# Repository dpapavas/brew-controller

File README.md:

<!-- -*- coding: utf-8 -*- -->

# Brew controller

This is a controller module designed as an add-on to the Gaggia Classic espresso
machine, although from a functional perspective it can be used with any "dumb"
espresso machine, i.e. any machine with a simple thermostat for boiler
temperature control and a simple on/off switch for pump control.  It can control
the brew process in both an automatic mode, following a programmed brew profile
based on flow, pressure and/or yield weight, or in manual mode, allowing direct,
real-time control of flow, pressure, or pump power.

## Design

The controller consists of the following parts:

* A pressure sensor, attached to the exit of the boiler, just before the group
  head.

* A flow sensor, attached to the pump inlet.

* A load cell, mounted below the drip tray, weighing the yielded coffee.

* A controller board, consisting of a pair of TRIAC switches, controlling power
  to the boiler and pump and a microcontroller, interfacing the sensors and
  controlling these switches.

* An enclosure and other assorted accessories, used to mount all the above to
  the espresso machine.

The design is freely available, but anyone considering their own build is urged
to read the discussion below, as there are some issues that will need to be
addressed.

## Operation

So, is this useful?  Well, yes, it is. All features, while arguably not
necessary, do offer additional useful control over the brewing process.
Temperature control improves temperature stability and control, allowing the
brewing to be adapted to the coffee at hand and, more importantly, improving the
consistency of the result across multiple shots.  Pump power control, makes
preinfusion possible and, in combination with pressure and flow measurement, it
also makes control of these parameters possible.  Pressure control is useful to
avoid channeling, while flow control can be useful, both to control preinfusion
where pressure has not yet developed and to give some control over brew time.
Weighing the yield allows automatic control of the brew ratio, as well as more
sensible variation of other parameters during the brew process (for instance the
pressure can be tapered off during the final third of the shot in terms of the
yield mass, instead of time).

The following plot is from data recorded by the controller during a programmed
shot.

The machine is already warmed up, as can be seen by the stable temperature (1)
and the small (less than 5% of the total) power needed at the boiler to maintain
it (2).  At about 12s the brew switch is pressed and the shot starts with a
preinfusion phase (3).  The pump is engaged at low power to push water through
the grounds at 3 ml/s.  As this happens, the temperature starts to drop, as cold
water enters the boiler, and power to the boiler is increased in order to
compensate.  Pressure gradually develops as the grounds expand and at 4 bars the
preinfusion phase is terminated (4).  Power to the pump is cut off, flow
vanishes and yield mass starts to rise as coffee starts to drip into the cup.

A blooming phase follows for the next 30s (5), where nothing much happens, apart
from temperature stabilization, a gradual drop-off in pressure and slight
increase in yield, as coffee leaks into the cup.  At 54s, the pump is engaged
once more, at higher power, and pressure is gradually ramped up to 9 bars (6).
Note the high initial flow, as the brew chamber is refilled, followed by a sharp
fall-off as the puck is compressed and pressure develops leading to oscillations
as the PID struggles somewhat to adapt to the complex dynamics.  This
necessitates both a gradual ramp-up in pressure (here from 0 to 9 bars in 5s) as
well as an additional wait time of 5s at 9 bars, while the flow settles.  After
that (7) the brew proceeds at constant flow rate, keeping the flow steady at the
1.7 ml/s it settled at.

In this particular shot, this strategy fails partially.  Maintaining the flow at
the instantaneous value measured at the end of the settling wait interval, leads
to a higher than desired flow and a pressure increase to a bit above 10 bars.
This can be corrected manually, if desired, either by reducing the flow to reduce
the developed pressure, or by reducing the pressure immediately.  No such action
has been taken here and the shot proceeds at a constant 10 bars and about 1.7
ml/s.  Note the disparity in volume and mass, the former of which is calculated
from the flow sensor, while the latter is measured via the load cell.  Some of
the difference is due to the water retained by the grounds, although most of
that has been accounted for, when the volume was reset at the end of the
preinfusion phase (4).  The rest of the difference is owed to inaccuracies in
the flow sensor, which accumulate as its signal is integrated to get the volume.

Finally the brew process is stopped at about 89s, with a total yield of 50g (8)
and pressure and flow drop to zero.  The sudden uptick in mass, is due to the
water remaining in the chamber being evacuated to the drip tray, via the
three-way solenoid valve.

A video recording of the controller brewing this exact shot, can be found
[here](https://youtu.be/QHlgAWKq7i8).

## Build

Although the design works quite well and is, at the time of this writing,
seemingly bug-free and refined enough for efficient and hassle-free daily use,
it does unfortunately suffer from a few design flaws that make it unsuitable for
anyone who might be considering building it.

For one, it was designed by someone that is not an electrical engineer.
Although as much care as possible was taken to ensure a good design, including
simulations and proper calculations where appropriate, the result does have a
few shortcomings which will probably need to be addressed:

* It is based on a Teensy 3.1/3.2 microcontroller, which is sadly no longer in
  production.  Any builds will therefore need to be ported to a more modern
  controller.  This problem is further compounded by the fact that the source
  code is "bare-metal", i.e. no hardware abstraction libraries are used, so that
  porting to a different controller is a non-trivial task.  Note though, that
  teasing out the application specific-code, i.e. the code implementing PID
  control, sensor signal reading and conditioning and rewriting the
  machine-specific parts, such as SPI, I2C, GPIO, timing and interrupt handling
  using a high-level library for the target controller, should not be a
  particularly hard task, given some experience.

* The coffee machine's brew switch, i.e. the one turning on the pump and
  starting the brewing process, is read through a GPIO input that is grounded
  via the switch.  The current design depends on the internal pull-up for this,
  which is too weak and hence prone to EMI.  This should probably be addressed in
  a potential board redesign, by including a stronger external pull-up resistor.

* In the current design, brewing is still controlled by the machine's brew
  switch, which is responsible for turning power to the pump on and off.  While
  this power can then be further controlled via the TRIAC, the three-way
  solenoid valve that is controlled by the same switch cannot.  Relegating this
  task to a relay, controlled by an additional GPIO output could therfore be
  useful, as it would allow automatically stopping the brew process, for
  instance when the desired yield has been achieved.  While this can be done
  now, one still needs to turn the switch off, to turn off the solenoid.  Doing
  this after the pump has been cut off, results in low pressure in the brew
  chamber and hence incomplete evacuation of the remaining brew water,
  nullifying the solenoid valve.

Due to the above, it is not expected that this design will be built by others.
The following discussion will therefore be limited to a general outline of the
build process.  Anyone intending to attempt a build is welcome to open an issue
for further clarifications.

### Parts

The parts needed to populate the board are the following:

|Designator|Description|
|----------|-----------|
|R3,R4|22KΩ, 1W through-hole resistor|
|R5|10KΩ, 1/4W through-hole resistor|
|U5|LD1117, 3.3V, TO-220-3 voltage regulator|
|C4,C2,C5|100nF through-hole ceramic resistor|
|D1|DB104, 400V, 1A bridge rectifier|
|R7,R6|360Ω, 1W through-hole resistor|
|Q1,Q2|2N7000, 0.2A, TO-92 N-Channel MOSFET|
|R8|680Ω, 1W through-hole resistor|
|U3,U2|MOC3021M, 400V optocoupler|
|Q3,Q4|BTA16-800CW 800V, TO-220-3 TRIAC|
|U4|Adafruit MAX31865 Module, or compatible|
|J4|JST XH 2-pin vertical connector|
|R2,R1|82Ω, 1/4W through-hole resistor|
|J2|Pin header, 2.54mm|
|J3|Pin header, 2.54mm|
|J5|Pin header, 2.54mm|
|U1|EL817 or PC817 optocoupler|
|C3|10u radial through-hole capacitor (low profile)|
|U6|Teensy 3.1 or 3.2|
|C1|100n, X2 through-hole capacitor|
|J1|5.08mm terminal block|

The following additional parts are also necessary:

* Heat sinks for the TRIACs.  Extruded aluminum heat sinks of size 46x20x10mm
  fit the enclosure and provide adequate cooling when properly mounted with heat
  sink compound.

* XP POWER ECL10US05-T 5V, 10W AC/DC power supply.

* Waveshare 1.5" RGB OLED Module, based on the SSD1351 controller.

* Waveshare rotation sensor, or similar push-button incremental rotary encoder.

* A PT100 temperature probe, preferably 3-wire.

* XDB-401 pressure sensor, in SS316L steel, 0-12 bar range, G1/8" thread, I2C
  interface.

* Shades Of Coffee Brew pressure gauge adaptor kit, or similar, along with a
  G1/8" female-to-female adaptor, to connect the pressure sensor to the boiler
  output.

* 3.3V hall-effect flow sensor.  The SEN-HZ06D can be used and has a suitably
  low range of 0.05-1.1 L/min.

* Adafruit NAU7802 24-Bit ADC module, or compatible.

* 1Kg 75x12.6x12.6mm load cell.  Mount holes should be M4, 10mm apart to fit the
  base and top plate.

* Shades of coffee slim drip tray.
 
* M3xM5x6mm threaded inserts for the enclosure.

* At least 1mm² silicon wire in various colors for high voltage/current wiring.

* Lower gauge silicon wire for the connection to the the espresso machine's brew
  switch.  Ideally of low enough gauge to allow crimping and fitting a
  Dupont-style terminal.

Finally, some parts need to be 3D printed.  See the [Things](#things) section
below.

# Assembly

Drill a total of six holes on the side of the espresso machine.  The 3D printed
mounting gasket can serve as a stencil to mark the locations and sizes of the
holes.  The four smaller peripheral holes serve to mount the enclosure.  Its
mounting bosses, where the threaded inserts are installed, should be able to
pass through those holes, barely protruding from the other side with the gasket
installed.  The two larger central holes serve to pass wiring into the espresso
machine.  One should be used for high voltage wiring and one for low voltage
wiring, to keep them separated.  Note that it is not absolutely necessary to
fully disassemble the espresso machine in order to drill the holes, although
that is the safest option.  With care, the operation can be carried out with
only the boiler screws and a few of its wires removed and the boiler simply held
out of the way, partially out of the machine.

Install the threaded inserts, assemble the controller board, including the
Teensy and TRIAC heat sinks and mount all boards onto the enclosure.  If the
supplied wiring brackets are used, it is recommended to glue the nuts on their
recesses, as they're otherwise held very loosely and can be a major source of
pain during assembly and repairs.

## Internal wiring

With the boards in place, the following internal wiring connections should be made:

* **Display module**: Attach the supplied 7-pin ribbon to the upper half
    (i.e. the part closest to the Teensy, marked `3V3`, `GND`, ..., `RST`) of
    the `J3` connector, noting the insertion orientation.

* **Rotary encoder**: Attach the supplied 5-pin ribbon to the `J2` connector on
    the board, noting the insertion orientation.

* **Supply**: Attach a suitable JST terminated cable from the output of the PSU
    board to the `J5` connector.  Although the connector is keyed, make sure the
    connector on the side of the controller board hasn't been soldered with
    incorrect orientation.  Also attach a 2-wire cable, terminated on one side
    with a suitable 3-pin JST connector to the input of the PSU board.  The bare
    wires on the other side, should be screwed into the terminal block plugged
    into the `J1` connector, in the pins marked `L` and `N`.  The polarity is
    not important.

After these steps, the assembled enclosure should look like this:

## Hardware assembly

Attach all external wiring (see below) to the appropriate controller connectors
and pass the wires through the two chassis holes, keeping high and low voltage
wires separated.  Place the enclosure so that the threaded bosses pass through
the holes drilled in the chassis and fasten it using the supplied countersunk
washers.  The lower washers can be hard to install, but it can be accomplished
using a short magnetic screw driver, if the boiler screws are removed and the
boiler moved out of the way, to gain access through the group head hole in the
chassis.  If the pressure sensor is used, its mount bracket should be used in
place of the washer for the upper hole closest to the middle of the machine.

Once the controller is fastened, the lower boiler thermostat should be removed
and replaced with the PT100 sensor.  The pressure sensor should also be
connected to the pressure gauge kit and mounted in the bracket, secured with a
zip tie passed through the slot in the back of the bracket.  The flow sensor
should be installed in line with the pressure inlet hose.

Two M4x12mm countersunk screws should be installed together with the supplied
"locating pins" in the holes at the top of the load cell base.  These form
locating bosses, mating with the holes at the bottom of the machine's chassis to
keep the base in place.  The load cell can be installed in either side, but the
right hand side is more convenient, as it facilitates the connections between
the controller module and both the load cell and the I2C bus.

The partially assembled scale looks like this:

The installed scale, can be seen [here](./doc/scale_installed.png).

## External wiring

The instructions below will be brief, intended more as a general strategy for
making the connections to the machine, rather than detailed instructions.  The
photograph should hopefully give a clearify the setup further, but please study
the wiring diagram first and take every care must be taken to ensure the proper
connections are made in a safe manner.

The proposed connections are for the EU model with the ECO timer module.  The
ECO timer will need to be bypassed, so as to gain access to a pair of contacts
at the brew switch for the controller sense connection. A simple wire with two
spade connectors is needed, but kits with installation instructions are also
sold online.

Note that live and neutral are treated loosely here and no care needs to or has
been taken to ensure that they correspond to the live and neutral at the
plug. They will therefore be indicated by "neutral" and "live" below.

### High voltage

* **"Neutral" input**: The "neutral" connection that powers the controller can
    be taken from the brew switch.  This requires a wire with three connectors
    on one end: one male spade connector plugging into the machine's "neutral"
    wire, after removing it from the brew switch, one female spade connector to
    restore the connection to the brew switch and another female spade
    connector, going back to the pump.

    The pump already has a connection for "neutral", but it passes through the
    brew switch, which creates a problem.  As the pump is switched off by the
    switch, back-EMF is created at the pump solenoid, leading to large voltage
    spikes and noise.  This can create all sorts of problems.  For instance it
    can pull the programming pin of the controller low and reboot it into
    programming mode, but it can also create I2C transmission problems, etc.
    Having an unswitched "neutral" connection allows the pump to be switched off
    via the TRIAC, which always ensures switching happens at zero current, hence
    no back-EMF or noise spikes.

    The other, unterminated end should be screwed into the controller's terminal
    block, at the place marked `N`, along with one of the small wires going to
    the PSU input.

* **"Live" input**: The live input can be taken from the lead going to the
    removed thermostat.  The other end should be screwed into to the
    controller's terminal block, at the place marked `L`, along with one of the
    other of the two small wires going to the PSU input.

* **Temperature control**: The other lead removed from the thermostat should be
    connected to the controller's terminal block, at the place marked `HEAT`.
    In this way, the controller's TRIAC switch essenatially assumes the place of
    the OEM thermostat switch.

* **Pump control**: The other terminal of the pump should be screwed into the
    controller's terminal block, at the place marked `PUMP`.  Note that the
    thermal fuse mounted on the pump is now by-passed.  It can be retained
    either by cutting and reusing the existing part, or by using a spare part,
    connected in-line with the wire going to the controller.

* **Solenoid snubber**: The three-way solenoid valve can generate noise, both
    due to the inrush current at turn-on, as well as due to the back-EMF induced
    voltage spike at turn-off.  The latter is more pronounced and can generate
    all sorts of havoc, such as resetting the controller, pulling encoder lines
    low generating phantom button presses, etc.  A simple (0.1 μF, 100 Ω, 1/2W,
    600 VAC) RC snubber should therefore be installed accross its line and
    neutral terminals to alleviate such problems.  Snubbers such as this can be
    readily found as a single discrete part, which, together with a few
    terminals and short wiring, can be attached to the valve without
    modifications to the OEM wiring.

### Low voltage

* **I2C bus**: A 4 core shielded cable should be used for the I2C bus.  At one
    end the following connections need to be made at the controller, at connetor
    `J3`:
        - `GND` to I2C ground
        - `PC2` to I2C +3.3V
        - `PB2` to I2C SCL
        - `PB3` to I2C SDA

    At the other end the cable should be connected to the pressure sensor and
    the load cell sensor board.  A thin enough cable can be routed through a gap
    in the mahine's chassis and behind and below the water tank.  The I2C wiring
    should be kept as short as possible, leaving enough slack to pull out the
    load cell frame when required.  The shield wire should be attached to the
    ground at both ends.

* **Flow sensor**: The wires from the flow sensor should be connected to the
    controller board, at connetor `J3`, as follows:
        - `PD5` to sensor +3.3V
        - `PD6` to sensor ground
        - `PC1` to sensour output

* **Temperature sensor**: The PT100 wires should be connected to the MAX31865
    module.  Consult its datasheet for the proper connections, as well as solder
    jumper configuration.

* **Brew switch sense**: The brew switch contacts left unused by the ECO timer
    by-pass should be connected to the controller, at the connetor `J5`.  One of
    the connectors pins is a ground pin and this should also be connected to the
    machine's chassis ground.  This connection serves to reference the
    controller's ground to the mains ground, preventing ground loops when the
    USB connector is attached to a mains-powered desktop computer.  It can be
    conveniently established with a female spade terminal, at the unused male
    spade forming part of the thermal fuse bracket screwed to the top of the
    boiler.

    A 100nF capacitor should also be soldererd between these two wires.  This
    serves to prevent votlage dips induced due to the large voltage (and hence
    current) differentials as the TRIAC switches the boiler on mid-cycle.

With all connections made, the machine's wiring should look similar to this:

# Software

To compile the firmware, you'll need the `gcc-arm-none-eabi` toolchain and the
Teensly CLI loader. With everything installed, compiling and loading the
firmware can be accomplished with:

```bash
$ cd src/
$ make all
$ make install
```

The firmware boots up in "automatic" mode; pressing the brew switch at this
point will execute the loaded program.  Pressing the encoder wheel button cycles
through the various manual modes, allowing manual control of the flow, pressure,
heat and pump power.  These are useful, both to execute on-the-fly, manually
controlled shot profiles, as well as to carry out various maintenance operations
(rinsing the group headed, backflushing, etc.).  Note that no manual control
over the scale is necessary, as it tares automatically, whenever a large enough
change in mass is detected (e.g. a cup or bean dosing tray is placed on it).

## USB console

With the controller connected to a computer via USB, a rudimentary serial
console is available, affording some manual control of the executing firmware,
as well as querying and logging its state.  How it can be accessed, depends on
your platform.  For instance, on GNU/Linux, it can be accomplished with the
`socat` program with:

```bash
$ socat - /dev/ttyACM0,raw,echo=0
```

The following commands are available:

* `r`: Reset the controller.
* `b`: Reboot the controller into programming mode.

* `l[t|p|m|f][N]`: Toggle logging of temperature (`t`),
    pressure (`p`), mass (`m`), or flow (`f`), or print `N` log lines if an
    optional trailing number is provided.  The output consists of lines of
    comma-separated values, corresponding to time, value, derivative, raw value,
    and raw code, respectively.  The value is the filtered instantaneous value
    of the logged parameter, with the unfiltered value also available, to aid in
    tuning the filtering if desired.  The raw code is the data read from the
    sensor; mostly useful in debugging sensor communication.  Free-running
    logging can be stopped by issuing any logging command, including a simple
    `l`.

    For example `lt10` would display 10 lines of temperature data, `lp` would
    turn on pump logging and `l` would turn it off again.

* `l(T|P|F)[N]`: Toggle logging of temperature (`T`), pressure
    (`P`), or flow (`F`) PID control.  Similar to the above, only the
    lines contain time, PID output (i.e. heat/pump power), PID input
    (i.e. temperature, pressure, etc.), PID set point and PID proportional,
    integral and derivative terms.  Useful in tuning the PID parameters.

* `ls[N]`: Toggle "shot" logging.  Similar to the above, but the lines contain
    time, temperature, pressure, flow, volume, mass and heat and pump power.
    Useful in producing shot graphs, such as the one in this document.

* `lc`: Toggles "click" logging, useful in debugging the operation of the
    rotary encoder wheel.

* `s[h|p][d|p|f][N]`: Without a setting `N`, prints the current heat (`h`) or
    pump (`p`), delay (`d`), power (`p`) or flow (`f`) setting.  All are
    expressed in percentages, from 0 to 100.  Delay is simply the dalay before
    the TRIAC turns on the device in question, i.e. the complement of duty.
    Power is a setting in terms of percent of full power, from which a delay
    setting is calculated.  Flow, is only accepted for the pump and is the same
    as power, with a slight normalization as anything below 20% power doesn't
    really produce any flow to speak ok.

    For example, `shp` would print the current heat power setting and `spd50`
    would turn on power to the pump for half the mains voltage cycle.

* `c[h|p|f][SET,Kp,Ti,Td]`: With no settings, prints current heat (`h`) pump
    (`p`), or flow (`f`) PID configuration as a series of comma-separated
    numbers, including set point, gain, integration time, derivative time and
    current error integral of the PID.  The first three of the above parameters
    can be changed, by specifying new values.  The integral is always reset when
    any PID configuration value is changed.

    For example, `ch94` will only change the temperature setpoint to 94 keeping
    other heat PID parameters unchanged, while `cp3,0.35` will set the pump PID
    to 3 bars with gain equal to 0.35.

* `ci[SLAVE,ADDR,VAL]`: Query or configure I2C devices.  With only the slave
    specified, probe this slave.  This will result in an error if the slave is
    not on-line.  If a register address is also specified, read this address and
    return its contents in decimal, hexadecimal and binary forms.  If a value is
    also specified, write this value to the specified address. All parameters
    are in hexadecimal notation.

    For example, `ci54,0` reads register 0 of the NAU78802, while `cida,1,20`
    writes 0x20 to register 1 of the NSA2862X inside the pressure sensor.

* `z[f|m]`: Resets the calculated volume (`f`) to zero, or tares mass
    (`m`).

* `p[l|,STAGE,...]`: Without any arguments, a plain `p` prints the current
    programmed brew profile.  When `l` is specified the last captured profile
    log is printed, otherwise programs the new brew profile.

    The program, consists of a set of stages, separated by commas.  Each stage
    is a separate phase of the brew process, where some output variable, which
    can be either flow (`f`), pressure (`p`) or pump power (`w`) is controlled
    based on some measured input variable, either shot time (`t`), current
    pressure (`p`), current flow (`f`), current volume (`v`), or current mass
    (`m`).  Conceptually, it can be though of as a graph, with the input
    (measured) variable on the x axis and the output (controlled) variable on
    the y axis.  Both axes can be specified in one of three modes: absolute
    (`a`) where the value is given in absolute terms, relative (`r`) where the
    value is given relative to what it was at the beginning of the phase and
    ratiometric (`q`) where it is specified as a multiple of what it was at the
    beginning of the phase.

    Each phase is specified as `input;output;point1;point2;...;commands`, where
    `input` and `output` each consist of two letters, specifying the input and
    output mode and variable, points are specified as `(x,y)` and commands can be
    one or more letters indicating that the shot time (`t`), volume (`v`), and
    mass (`m`) should be reset at the end of the phase, or `b`, which moves back
    one section, allowing unconditional looping.  Both the input and output
    values of the first point on each phase may be absent, indicating that the
    current value should be used.

    Consider the following program for example:

    ```
    ap;af;(0,3);(4,3);v,rt;ap;(0,);(1,0);(30,0);(35,9);(40,9);,av;qf;(0,);(+inf,1);
    ```

    It has three phases: the first preinfusion phase (`ap;af;(0,3);(4,3);v`)
    controls flow based on pressure and specifies a constant flow of 3 ml/s
    until the pressure reaches 4 bars.  The volume is then reset as we don't
    care about the water in the puck, only the yield.  The next phase
    (`rt;ap;(0,);(1,0);(30,0);(35,9);(40,9);`), controls pressure base on
    relative time, dropping the pressure to 0 within 1 second and keeping it
    there for 29 more seconds, until half a minute has passed from the beginning
    of the second phase.  The pressure is then ramped up to 9 bars in 5s and
    kept there for 5s more.  Finally the third phase (`rt;qf;(0,);(+inf,1);`)
    controls ratiometric flow based on relative time, and essentially keeps
    whatever flow resulted from the ramp-up to 9 bars at the end of the previous
    phase constant (a ratio of 1) forever, which is to say, until the brew
    switch is turned to the off position.

# Things

|STL|Description|
|---|-----------|
|[things/enclosure.stl](./things/enclosure.stl)|The enclosure for the controller board and peripherals.  It is mounted onto the side of the espresso machine.|
|[things/controller_bracket.stl](./things/controller_bracket.stl)|A bracket that can be mounted on the controller board, to serve as a tying post for the wiring.|
|[things/psu_bracket.stl](./things/psu_bracket.stl)|Same as above, for the PSU board.|
|[things/mount_gasket.stl](./things/mount_gasket.stl)|A gasket, to be printed in TPU and placed between the enclosure and the espresso machine's chassis.|
|[things/mount_washer.stl](./things/mount_washer.stl)|At least three of these are necessary; four if not using the pressure sensor mount.  They're used as washers for the M3 countersunk screws fastening the enclosure onto the machine's side.|
|[things/knob.stl](./things/knob.stl)|A knob for the rotary enocoder.  This is optional; any compatible knob can be used.|
|[things/knob_sleeve.stl](./things/knob_sleeve.stl)|A rubber sleeve for the knob, to be printed in TPU.|
|[things/nut.stl](./things/nut.stl)|An M7 flanged nut for the rotary encoder.  Not needed if one was supplied with the encoder.|
|[things/usb_plug.stl](./things/usb_plug.stl)|A plug for the USB port opening, to be printed in TPU.|
|[things/sensor_mount.stl](./things/sensor_mount.stl)|A mount bracket for the pressure sensor.|
|[things/load_base.stl](./things/load_base.stl)|The base of the weighing assembly, mounted in the place of the OEM drip tray.|
|[things/load_pin.stl](./things/load_pin.stl)|Locating pins, fastened with M4 countersunk screws on the bottom of the base, mating with the holes on the bottom of the espresso machine.|
|[things/load_plate.stl](./things/load_plate.stl)|The top plate, mounted on the load cell.|
|[things/load_plate_frame.stl](./things/load_plate_frame.stl)|A rubber frame for the top plate, to be printed in TPU and glued onto it.|

These designs were created using [Gamma](https://github.com/dpapavas/gamma) and
can therefore be modified to suit different parts or layouts.  Their source
files are located in
[/scheme](https://github.com/dpapavas/brew-controller/tree/master/scheme).

# Simulations

The simulations in [spice/](./spice) can be run with
[ngspice](https://ngspice.sourceforge.io/) and
[lepton-eda](https://github.com/lepton-eda/lepton-eda).  They include
simulations for the TRIAC drivers and RC snubber and can be useful when trying
out modifications to these circuits.

The following files are also needed to run the simulations, but haven't been
added to the distribution, since they are proprietary.  They can be readily
downloaded from the part manufacturers websites:

- `spice/1n4007.rev0.lib`
- `spice/2n7000.rev0.lib`
- `spice/MOC302X.lib`
- `spice/st_standard_snubberless_triacs.lib`

## License

The Scheme code in [scheme/](./scheme), is distributed under the [GNU
Affero General Public License Version 3](./LICENSE.AGPL).

The firmware sources in [src/](./src), as well as the controller PCB
design residing in [kicad/](./kicad/), is distributed under the [GNU
General Public License Version 3](./LICENSE.GPL).

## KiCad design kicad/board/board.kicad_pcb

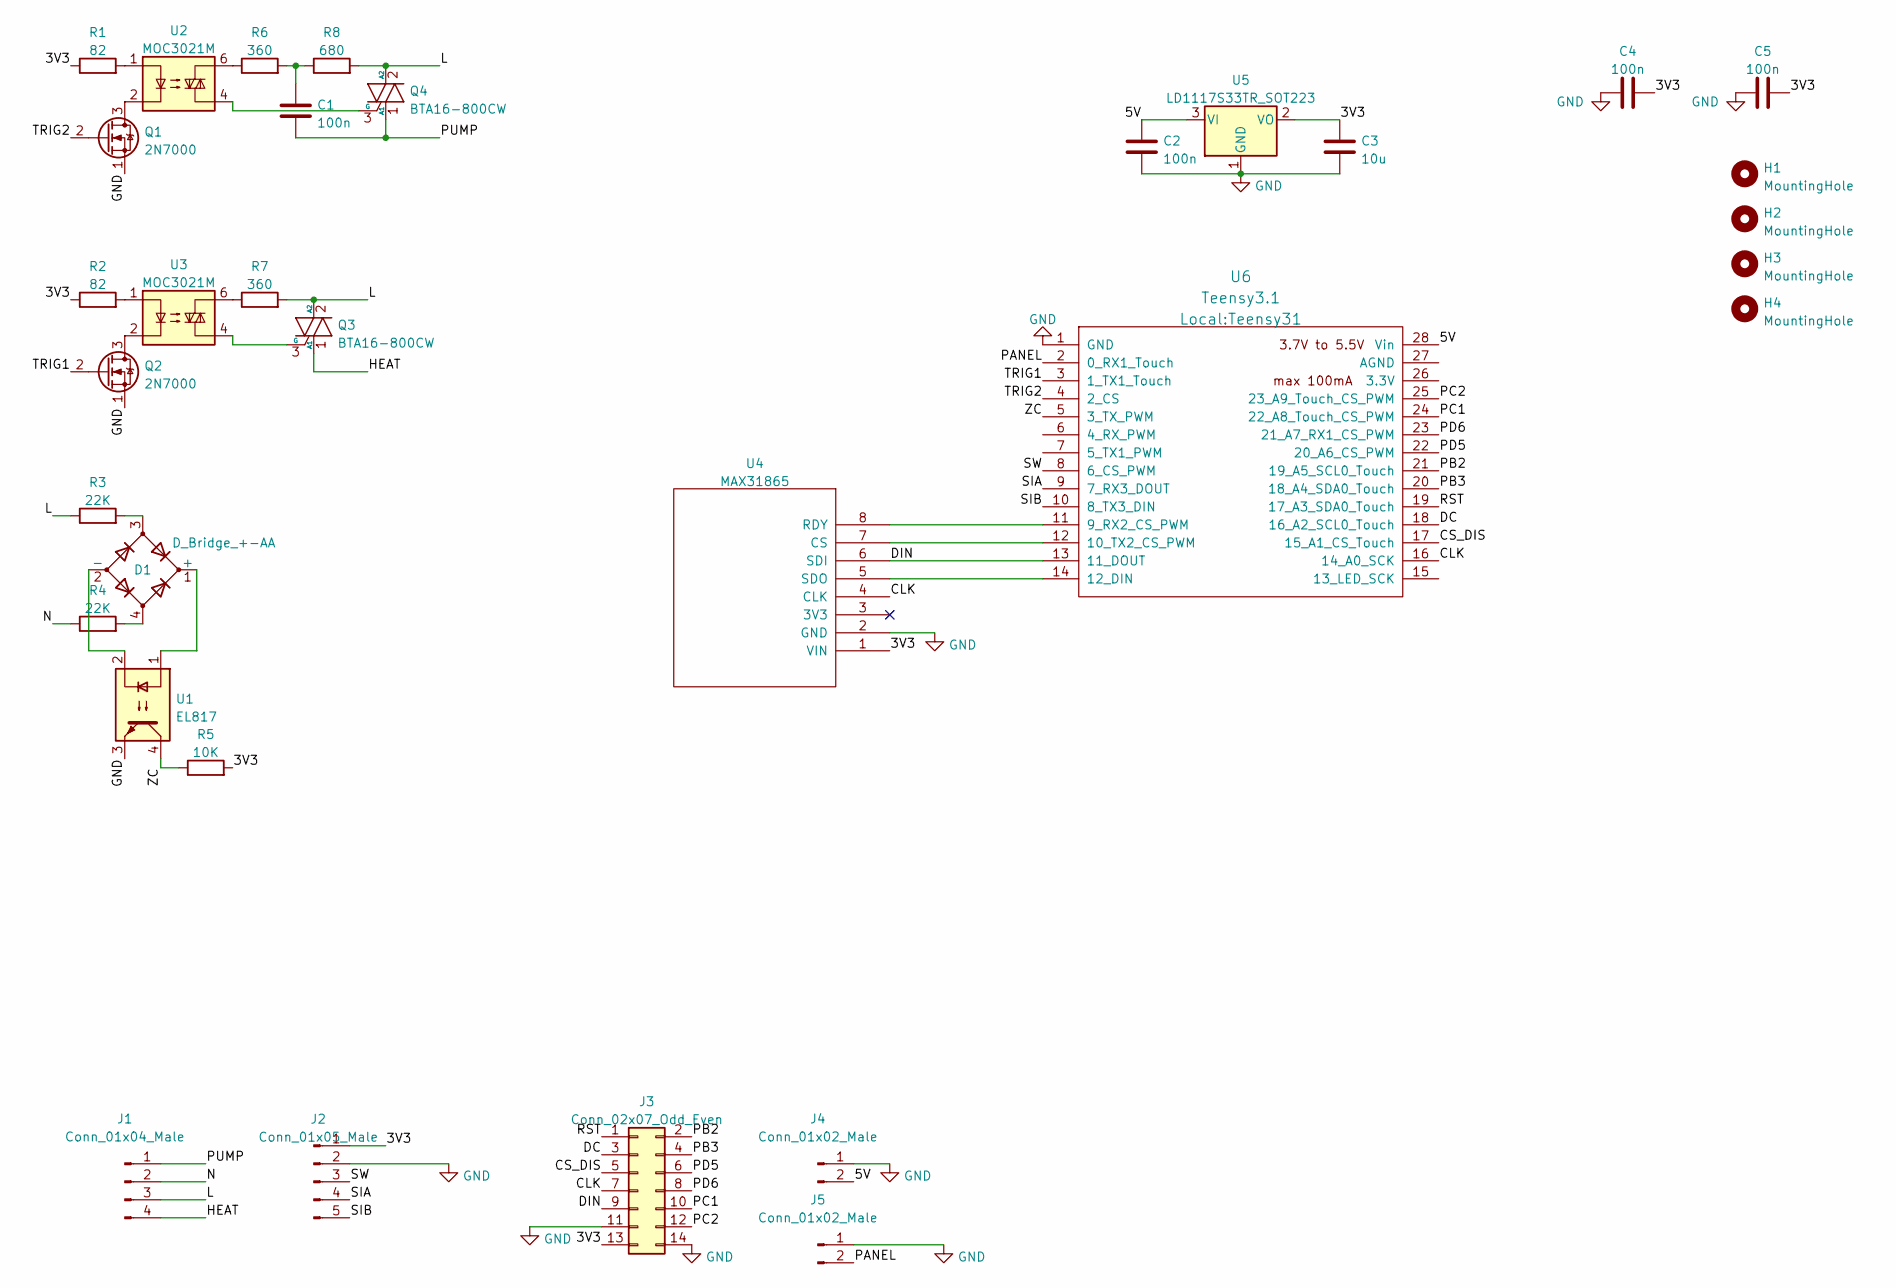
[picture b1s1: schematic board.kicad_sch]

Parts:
C1: 100n; C_Rect_L18.0mm_W6.0mm_P15.00mm_FKS3_FKP3
C2, C4, C5: 100n; C_Disc_D5.0mm_W2.5mm_P2.50mm
C3: 10u; CP_Radial_D5.0mm_P2.50mm
D1: D_Bridge_+-AA; Diode_Bridge_DIP-4_W7.62mm_P5.08mm
H1, H2, H3, H4: MountingHole; MountingHole_2.7mm_M2.5_ISO7380
J1: Conn_01x04_Male; TerminalBlock-4_P5.08mm
J2: Conn_01x05_Male; PinHeader_1x05_P2.54mm_Vertical
J3: Conn_02x07_Odd_Even; PinHeader_2x07_P2.54mm_Vertical
J4: Conn_01x02_Male; JST_XH_B2B-XH-AM_1x02_P2.50mm_Vertical
J5: Conn_01x02_Male; PinHeader_1x02_P2.54mm_Vertical
Q1, Q2: 2N7000; TO-92_Inline_Wide
Q3, Q4: BTA16-800CW; TO-220-3_Vertical_Heatsink
R1, R2: 82; R_Axial_DIN0207_L6.3mm_D2.5mm_P7.62mm_Horizontal
R3, R4: 22K; R_Axial_DIN0309_L9.0mm_D3.2mm_P12.70mm_Horizontal
R5: 10K; R_Axial_DIN0207_L6.3mm_D2.5mm_P7.62mm_Horizontal
R6, R7: 360; R_Axial_DIN0309_L9.0mm_D3.2mm_P12.70mm_Horizontal
R8: 680; R_Axial_DIN0309_L9.0mm_D3.2mm_P12.70mm_Horizontal
U1: EL817; DIP-4_W7.62mm
U2, U3: MOC3021M; DIP-6_W7.62mm
U4: MAX31865; MAX31865 Module
U5: LD1117S33TR_SOT223; TO-220-3_Horizontal_TabDown
U6: Teensy3.1; Teensy31

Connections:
/3V3: C3.1, C4.2, C5.2, J2.1, J3.13, R1.1, R2.1, R5.2, U4.1 (VIN), U5.2 (VO)
/5V: C2.1, J4.2, U5.3 (VI), U6.28 (Vin)
/CLK: J3.7, U4.4 (CLK), U6.16 (14_A0_SCK)
/CS_DIS: J3.5, U6.17 (15_A1_CS_Touch)
/DC: J3.3, U6.18 (16_A2_SCL0_Touch)
/DIN: J3.9, U4.6 (SDI), U6.13 (11_DOUT)
/HEAT: J1.4, Q3.1 (A1)
/L: J1.3, Q3.2 (A2), Q4.2 (A2), R3.1, R7.2, R8.2
/N: J1.2, R4.1
/PANEL: J5.2, U6.2 (0_RX1_Touch)
/PB2: J3.2, U6.21 (19_A5_SCL0_Touch)
/PB3: J3.4, U6.20 (18_A4_SDA0_Touch)
/PC1: J3.10, U6.24 (22_A8_Touch_CS_PWM)
/PC2: J3.12, U6.25 (23_A9_Touch_CS_PWM)
/PD5: J3.6, U6.22 (20_A6_CS_PWM)
/PD6: J3.8, U6.23 (21_A7_RX1_CS_PWM)
/PUMP: C1.2, J1.1, Q4.1 (A1)
/RST: J3.1, U6.19 (17_A3_SDA0_Touch)
/SIA: J2.4, U6.9 (7_RX3_DOUT)
/SIB: J2.5, U6.10 (8_TX3_DIN)
/SW: J2.3, U6.8 (6_CS_PWM)
/TRIG1: Q2.2 (G), U6.3 (1_TX1_Touch)
/TRIG2: Q1.2 (G), U6.4 (2_CS)
/ZC: R5.1, U1.4, U6.5 (3_TX_PWM)
GND: C2.2, C3.2, C4.1, C5.1, J2.2, J3.11, J3.14, J4.1, J5.1, Q1.1 (S), Q2.1 (S), U1.3, U4.2 (GND), U5.1 (GND), U6.1 (GND)
unnamed: C1.1, R6.2, R8.1
unnamed: D1.1 (+), U1.1
unnamed: D1.2 (-), U1.2
unnamed: D1.3, R3.2
unnamed: D1.4, R4.2
unnamed: Q1.3 (D), U2.2
unnamed: Q2.3 (D), U3.2
unnamed: Q3.3 (G), U3.4
unnamed: Q4.3 (G), U2.4
unnamed: R1.2, U2.1
unnamed: R2.2, U3.1
unnamed: R6.1, U2.6
unnamed: R7.1, U3.6
unnamed: U4.5 (SDO), U6.14 (12_DIN)
unnamed: U4.7 (CS), U6.12 (10_TX2_CS_PWM)
unnamed: U4.8 (RDY), U6.11 (9_RX2_CS_PWM)

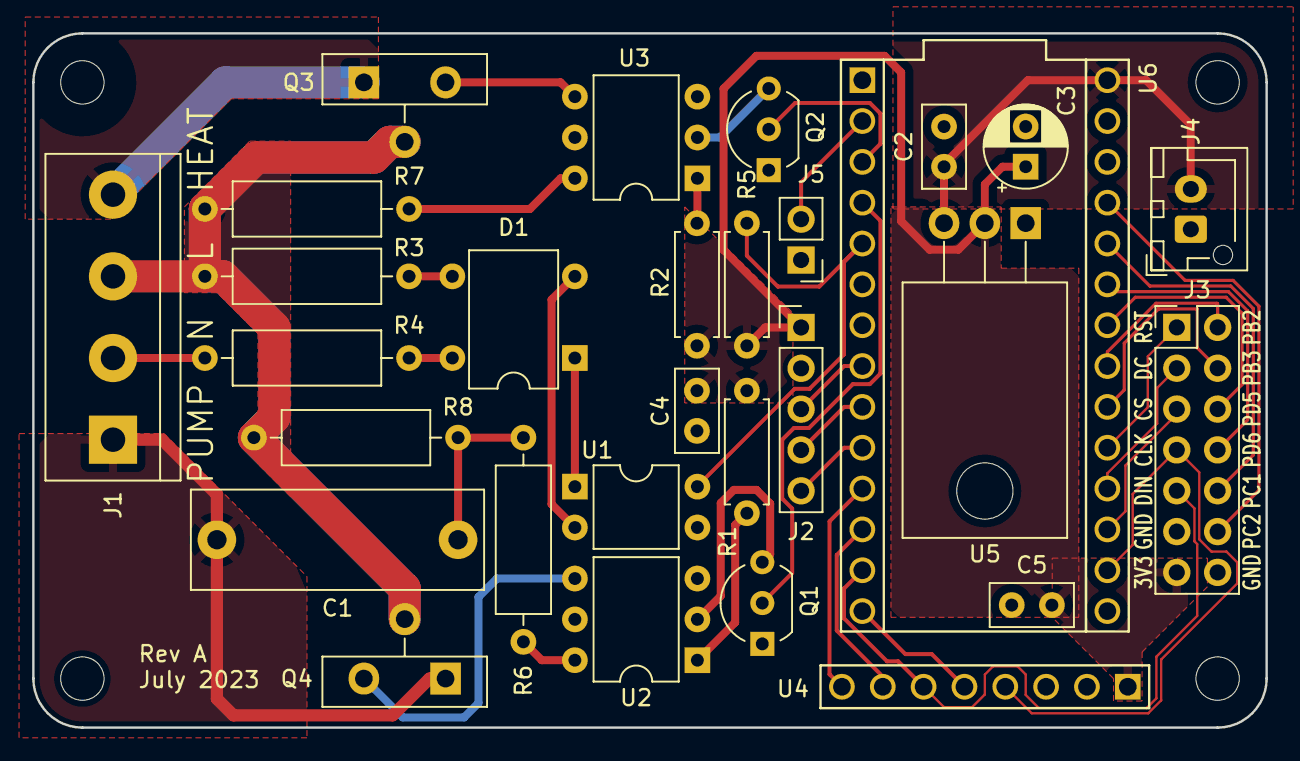
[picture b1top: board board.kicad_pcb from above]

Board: 2 copper layers, 76.7 x 43.2 mm, 33 parts (0 on the bottom side), 41 nets.

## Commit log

2024-02-15 Import the sources into Git.
2024-02-15 Add prebuilt STL files.
2024-02-15 Add copyright notices.
2024-03-12 Add documentation.
2024-03-12 --amend
2024-06-30 Add diagnostic functionality.
2024-11-17 Improve the enclosure; switch to heat-set threaded inserts.
2024-11-20 Enable encoder input pull-ups.
2024-11-21 Improve profiling.
2024-11-21 Add profile logging.

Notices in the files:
README.md:
License:
The Scheme code in [scheme/](./scheme), is distributed under the [GNU
Affero General Public License Version 3](./LICENSE.AGPL).
The firmware sources in [src/](./src), as well as the controller PCB
design residing in [kicad/](./kicad/), is distributed under the [GNU
General Public License Version 3](./LICENSE.GPL).
